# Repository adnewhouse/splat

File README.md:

# Splat Rocket Flight Computer

Splat is a simple data logger/flight computer for hobby-class rockets. 

Current featureset includes:
- Teensy 3.6 for main CPU
- BMP380 Barometer
- 4x Pyro output channels (with continuity check and fire verification)
- Support for external GPS module
- Buzzer
- Dual RGB LEDs
- 3x Servo channels for TVC
- LoRa Radio Module for telemetry and real time data
- ISM330DLC 6-axis IMU
- MicroSD card for data logging
- SPI flash for faster data rate logging

# Project Status

Splat is still in the stages of schematic capture

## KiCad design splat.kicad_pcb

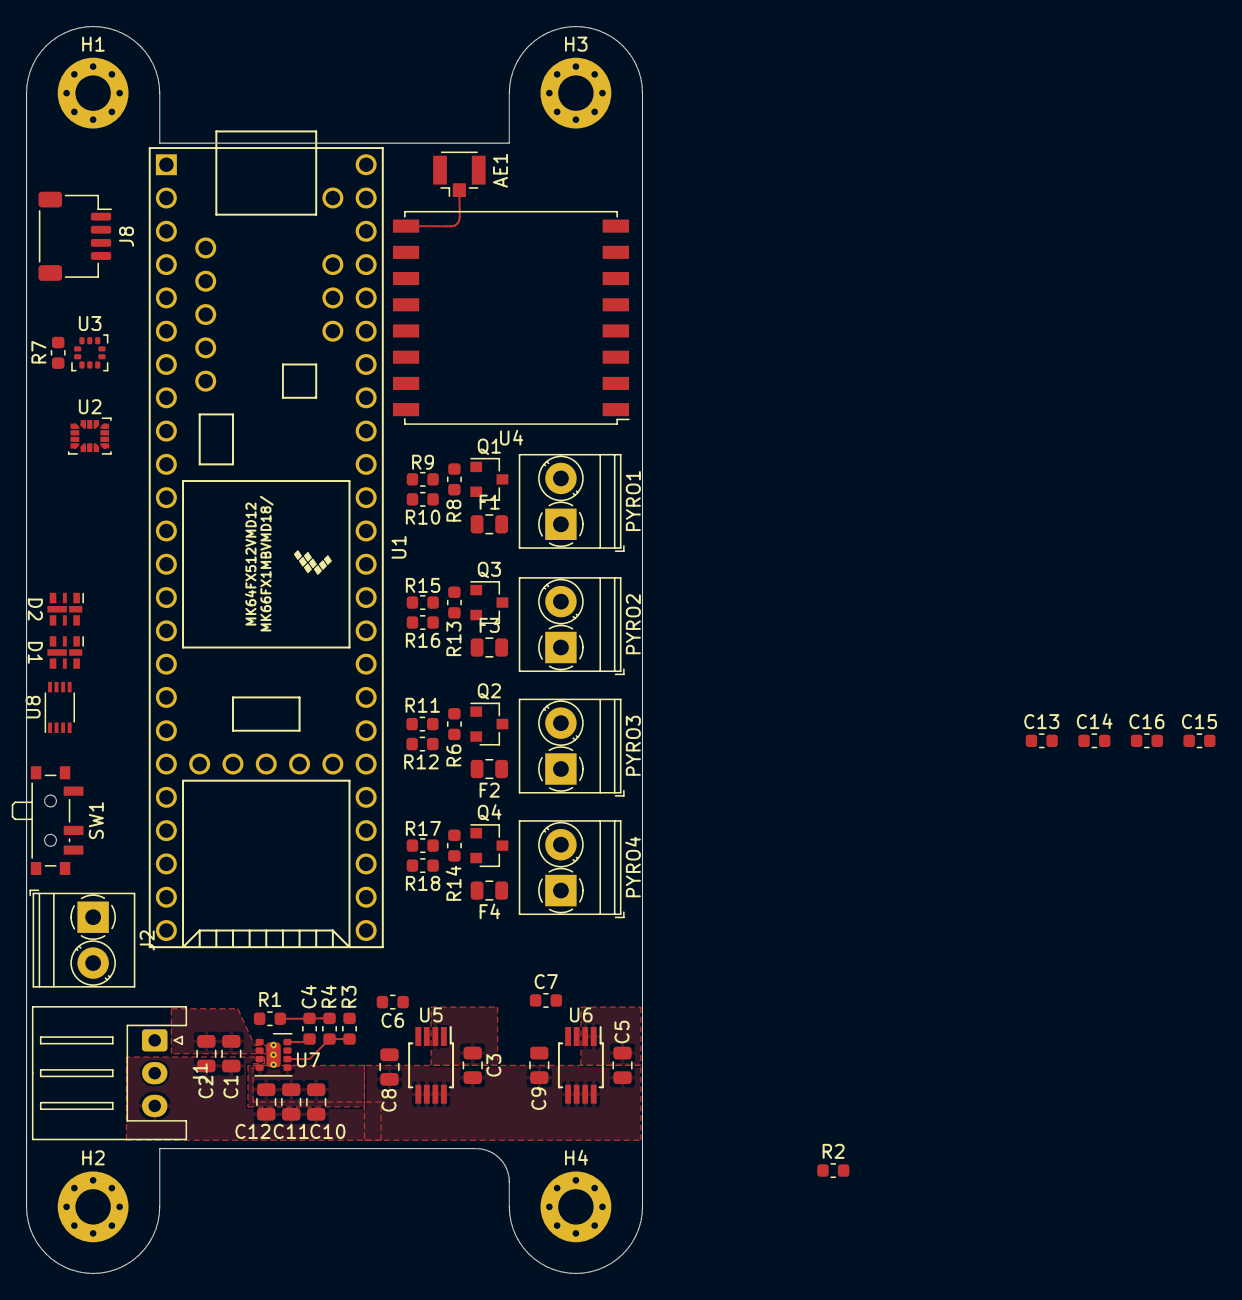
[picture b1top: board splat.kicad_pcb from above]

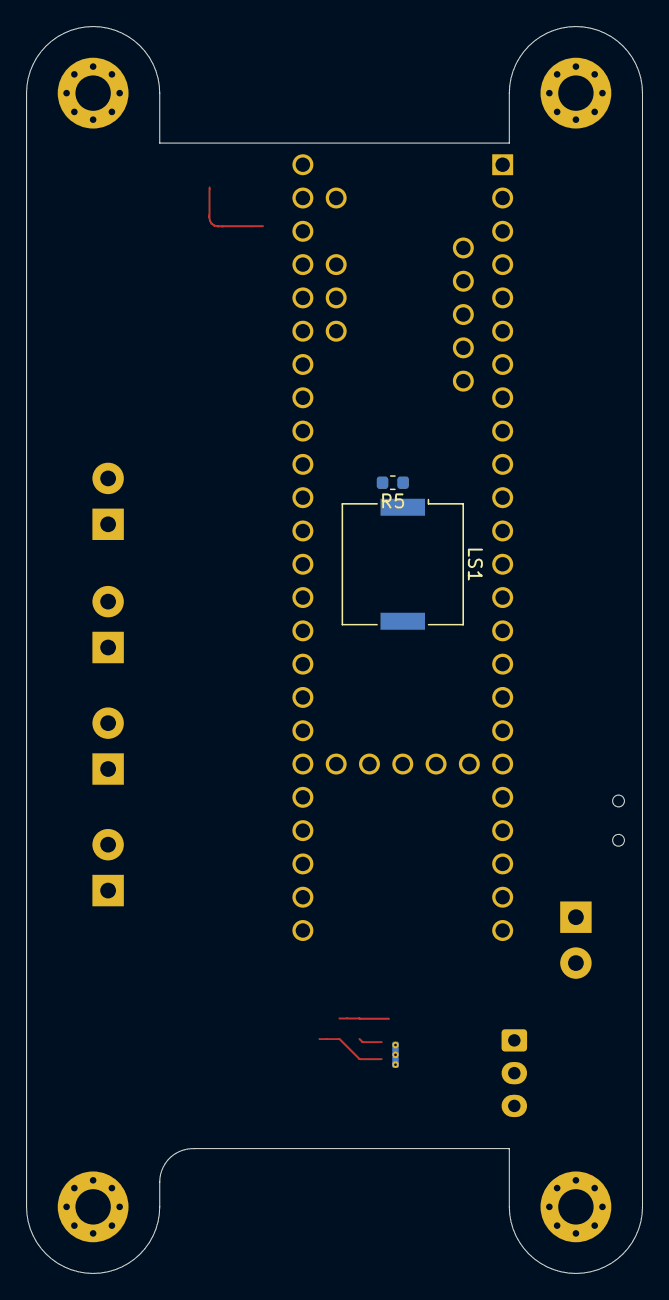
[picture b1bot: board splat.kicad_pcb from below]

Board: 4 copper layers, 47.0 x 95.1 mm, 66 parts (2 on the bottom side), 49 nets.

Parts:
AE1: Antenna_Shield; U.FL_Hirose_U.FL-R-SMT-1_Vertical
C1, C2: 10uF; C_0805_2012Metric
C3, C5: 1uF; C_0805_2012Metric
C4: 430pF; C_0603_1608Metric
C6, C7: 680pF; C_0603_1608Metric
C8, C9: 2.2uF; C_0805_2012Metric
C10, C11, C12: 22uF; C_0805_2012Metric
C13, C15: 100nF; C_0603_1608Metric
C14, C16: 1uF; C_0603_1608Metric
D1, D2: APA102-2020; LED-APA102-2020
F1, F2, F3, F4: Polyfuse; Fuse_0805_2012Metric
H1, H2, H3, H4: MountingHole_Pad; MountingHole_2.7mm_Pad_Via
J1: BATT; JST_XH_S3B-XH-A_1x03_P2.50mm_Horizontal
J2: EXT_SW; TerminalBlock_Phoenix_PT-1,5-2-3.5-H_1x02_P3.50mm_Horizontal
J4: PYRO1; TerminalBlock_Phoenix_PT-1,5-2-3.5-H_1x02_P3.50mm_Horizontal
J5: PYRO3; TerminalBlock_Phoenix_PT-1,5-2-3.5-H_1x02_P3.50mm_Horizontal
J6: PYRO2; TerminalBlock_Phoenix_PT-1,5-2-3.5-H_1x02_P3.50mm_Horizontal
J7: PYRO4; TerminalBlock_Phoenix_PT-1,5-2-3.5-H_1x02_P3.50mm_Horizontal
J8: Conn_01x04; JST_SH_SM04B-SRSS-TB_1x04-1MP_P1.00mm_Horizontal
LS1: Speaker_Crystal; Buzzer_Murata_PKMCS0909E4000-R1
Q1, Q2, Q3, Q4: NTR4501NT1G; SOT-23
R1, R2, R4, R10, R12, R16, R18: 100K; R_0603_1608Metric
R3: 523K; R_0603_1608Metric
R5: 1K; R_0603_1608Metric
R6, R7, R8, R13, R14: 10K; R_0603_1608Metric
R9, R11, R15, R17: 300K; R_0603_1608Metric
SW1: PWR; SW_SPDT_PCM12
U1: TEENSY3.6; Teensy35_36
U2: ISM330DLC; LGA-14_3x2.5mm_P0.5mm_LayoutBorder3x4y
U3: BMP380; ST_HLGA-10_2.5x2.5mm_P0.6mm_LayoutBorder3x2y
U4: RFM96W-433S2; HOPERF_RFM9XW_SMD
U5, U6: MIC5219-3.3YMM; MSOP-8_3x3mm_P0.65mm
U7: TPS82140; Texas_SIL0008D_MicroSiP-8-1EP_2.8x3mm_P0.65mm_EP1.1x1.9mm_T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
U8: 74LVC2T45DC; VSSOP-8_2.3x2mm_P0.5mm

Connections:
+3V3: C9.1, J8.1, U4.13, U6.3, U8.1
+BATT: C1.1, C2.1, C3.1, C5.1, F1.1, F2.1, F3.1, F4.1, SW1.1, U5.2, U6.1, U6.2, U7.2
/3V3_AUX: C8.1, C13.1, C14.1, C15.1, C16.1, R7.1, U2.5, U2.8, U3.1, U3.10, U5.3
/3V3_AUX_EN: R2.1, U5.1
/5V_EN: R1.1, U7.1
/5V_SERVO: C10.1, C11.1, C12.1, D1.1, D2.1, R3.1, U7.4, U7.5, U8.8
/BEEPER: LS1.1, R5.1
/BMP_INT: R7.2, U1.36, U3.7
/CS_RF: U1.12, U4.5
/IMU_INT1: U1.44, U2.4
/IMU_INT2: U1.43, U2.9
/MISO_0: U1.14, U4.2
/MOSI_0: U1.13, U4.3
/PYRO1_EN: Q1.1, R8.1, U1.2
/PYRO1_SENSE: R9.2, R10.1, U1.42
/PYRO2_EN: Q3.1, R13.1, U1.3
/PYRO2_SENSE: R15.2, R16.1, U1.41
/PYRO3_EN: Q2.1, R6.1, U1.4
/PYRO3_SENSE: R11.2, R12.1, U1.38
/PYRO4_EN: Q4.1, R14.1, U1.5
/PYRO4_SENSE: R17.2, R18.1, U1.37
/RF_DIO0: U1.57, U4.14
/RF_DIO1: U1.56, U4.15
/RF_DIO2: U1.50, U4.16
/RF_DIO3: U1.49, U4.11
/RF_DIO4: U1.48, U4.12
/RF_DIO5: U1.47, U4.7
/RXD_GPS: J8.3, U1.19
/TXD_GPS: J8.2, U1.18
GND: AE1.2, C1.2, C2.2, C3.2, C4.2, C5.2, C6.2, C7.2, C8.2, C9.2, C10.2, C11.2, C12.2, C13.2, C14.2, C15.2, C16.2, D1.6, D2.6, J1.3, J8.4, LS1.2, Q1.2, Q2.2, Q3.2, Q4.2, R1.2, R2.2, R4.2, R5.2, R6.2, R8.2, R10.2, R12.2, R13.2, R14.2, R16.2, R18.2, U1.1, U1.27, U1.39, U1.52, U2.6, U2.7, U3.3, U3.8, U3.9, U4.1, U4.8, U4.10, U5.5, U5.6, U5.7, U5.8, U6.5, U6.6, U6.7, U6.8, U7.3, U7.9, U8.4
unnamed: AE1.1, U4.9
unnamed: C4.1, U7.8
unnamed: C6.1, U5.4
unnamed: C7.1, U6.4
unnamed: D1.2, D2.5
unnamed: D1.3, D2.4
unnamed: D1.4, U8.7
unnamed: D1.5, U8.6
unnamed: F1.2, J4.1
unnamed: F2.2, J5.1
unnamed: F3.2, J6.1
unnamed: F4.2, J7.1
unnamed: J1.1, J2.1
unnamed: J2.2, SW1.2
unnamed: J4.2, Q1.3, R9.1
unnamed: J5.2, Q2.3, R11.1
unnamed: J6.2, Q3.3, R15.1
unnamed: J7.2, Q4.3, R17.1
unnamed: R3.2, R4.1, U7.6

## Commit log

2019-09-21 add kicad files
2019-09-21 Add pyro sense
2019-09-21 README.md
2019-09-24 Add teensy 3.6, add IMU, start connecting important nets
2019-09-24 Start layout, add 3d files
2019-09-26 Layout and servo connectors
2019-10-18 Add render
